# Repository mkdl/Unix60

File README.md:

# Unix60
The Unix60 is a budget FR4 keyboard designed to make a HHKB-style layout available to everyone with as few compromises as possible.

If you have any questions or need help, please join the FR4 Discord: https://discord.gg/z7mpQX5YJQ

### Disclaimer: You must follow this guide in the order it is written. Assembling stuff in the wrong order (specifically your Pro Micro or Elite C and its headers) will likely result in you having to desolder components and significantly increase the amount of time it takes to assemble. I am not responsible for boards damaged during assembly. I highly recommend you read through the entire guide before starting assembly.

# Assembly:

### 1. Put the diodes through the PCB so the legs stick out the front side of the board and so the diode is flush with the back, making sure the black line on the diode faces the square pad:

### 2. Solder from the back and snip the legs:

### 3. Place your Pro Micro or Elite C onto its pin headers and sit it into the board so the Pro Micro is on the back of the PCB (the side with the Unix60 logo) and tape it down to temporarily hold it in place. This helps align the pin headers properly. It doesn't matter whether you put the shorter pins on the PCB or the longer ones; either way, you will have to snip the longer ones once you've soldered them in. **DO NOT SOLDER THE PRO MICRO OR ELITE C TO THE PIN HEADERS YET!**

### 4. Solder in the pin headers from the front side of the PCB. **Do not solder the Pro Micro or Elite C yet, just the headers!**

### 5. Solder your reset button to the PCB 

### Note: If you've lost your reset button, don't worry. Shorting the two pads closest to the edge of the PCB or the two closest to the inside will reset your controller. After all, that's all the button does :)
### 8. Attach your stabs to the PCB (do not be afraid to push, you won't break it)

### 9. Mount switches in the corner of the plate to align it, then lower the plate onto the PCB

### 10. Add the rest of your switches and solder them all in

### 11. Once you have verified that all your diodes, switches, and Pro Micro or Elite C pin headers are soldered properly, you can now solder your Pro Micro or Elite C onto the pin headers:

### 12. Attach standoffs to the bottom of the plate using screws from the other side, you may need to cut of the long pins on your controller board if the bottom plate wont fit on.

### 13. Screw on the bottom plate
# Flashing instructions for Linux:
### 1. Plug your Pro Micro or Elite C in
### 2. Open up the [QMK configurator](https://config.qmk.fm/#/fr4/unix60/LAYOUT_all) and create your desired layout
### 3. Download the .json file (on the left, next to keymap.json)
### 4. Open up a command line
### 5. Type ```qmk flash /path/to/layout.json``` (obviously replacing the file path with the path to your downloaded layout) and follow any additional instructions
### One thing to note is that you can compile a .hex file on the configurator and flash that with avrdude, however, I prefer the method outlined above.
# Flashing instructions for Windows:
### Please keep in mind that I do not run Windows on my own system and cannot 100% verify this flashing procedure will work or if it requires any other configuration. I highly recommend you check the QMK docs if something is not working. 
### 1. Plug your Pro Micro or Elite C in
### 2. Open up the [QMK configurator](https://config.qmk.fm/#/fr4/unix60/LAYOUT_all) and create your desired layout
### 3. Click "compile" in the upper right, and once it's done, download the .hex by clicking "firmware"
### 4. Open up [QMK toolbox](https://github.com/qmk/qmk_toolbox/releases) and load your downloaded .hex
### 5. Click "flash" and follow any additional instructions - you may need to click reset for QMK Toolbox to figure out there is a flashable device.

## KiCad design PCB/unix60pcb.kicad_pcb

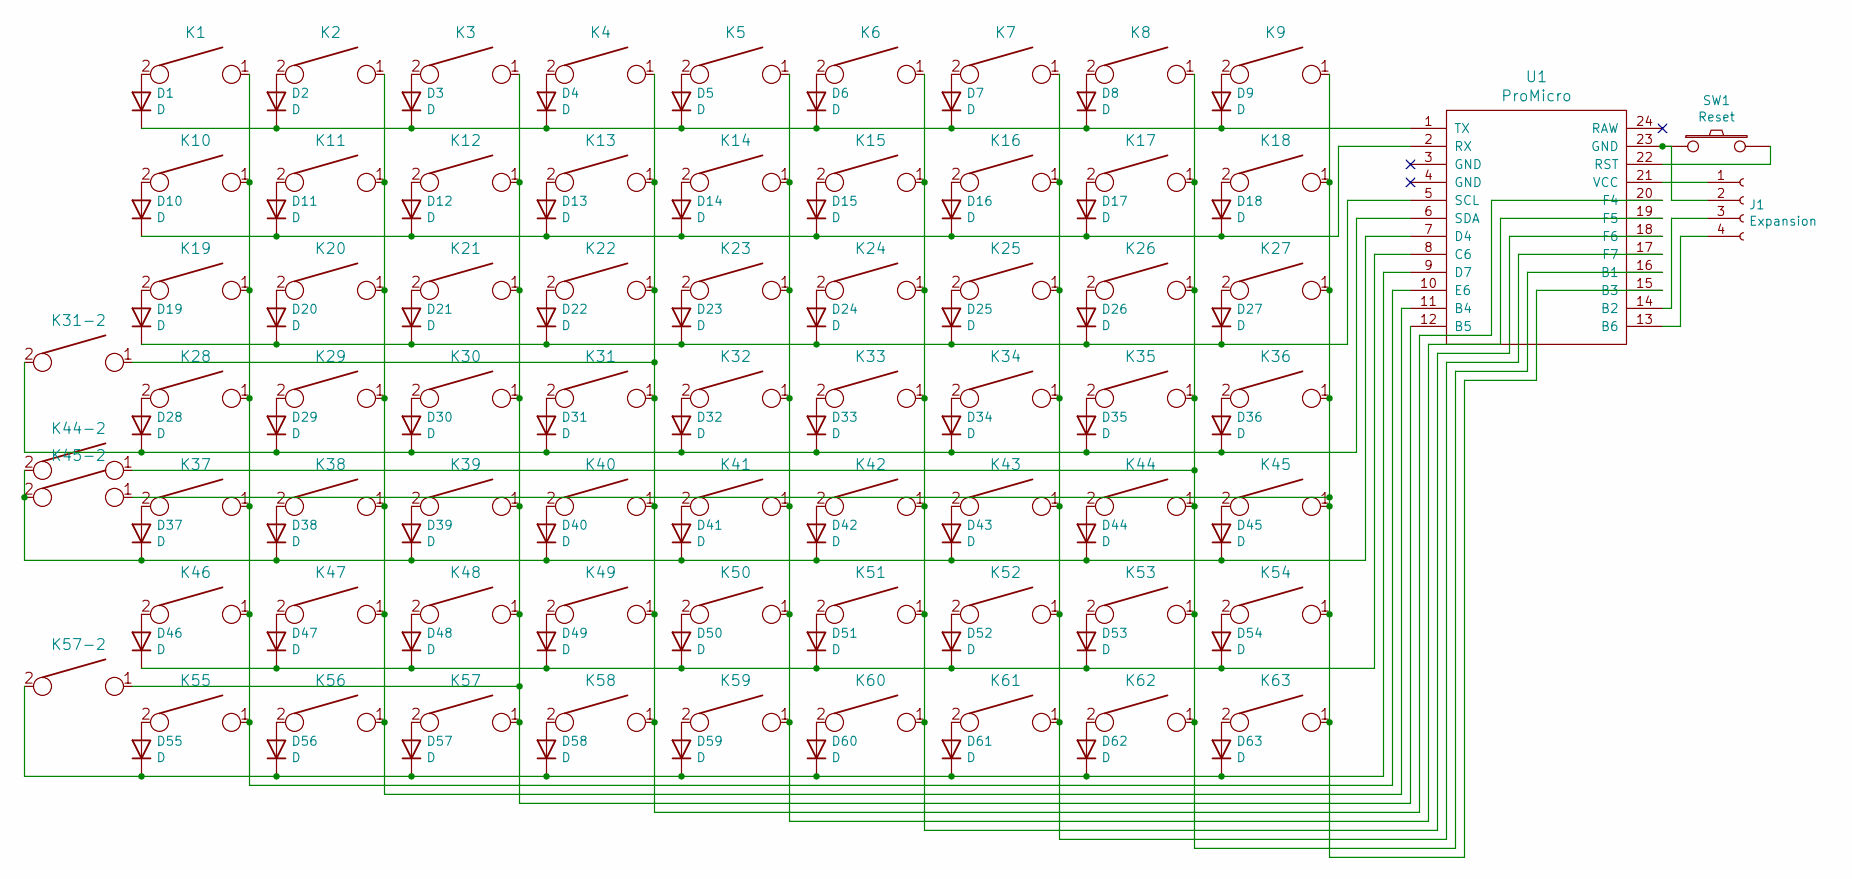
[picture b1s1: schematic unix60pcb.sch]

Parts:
D1, D2, D3, D4, D5, D6, D7, D8, D9, D10, D11, D12, D13, D14, D15, D16, D17, D18, D19, D20, D21, D22, D23, D24, D25, D26, D27, D28, D29, D30, D31, D32, D33, D34, D35, D36, D37, D38, D39, D40, D41, D42, D43, D44, D45, D46, D47, D48, D49, D50, D51, D52, D53, D54, D55, D56, D57, D58, D59, D60, D61, D62, D63: D; D_SOD123_axial-dual
J1: Expansion; PinSocket_1x04_P2.54mm_Vertical
K1, K2, K3, K4, K5, K6, K7, K8, K9, K10, K11, K12, K13, K14, K16, K18, K19, K20, K21, K22, K23, K24, K25, K26, K27, K28, K29, K32, K33, K34, K35, K36, K37, K38, K39, K40, K41, K42, K43, K46, K47, K48, K49, K50, K51, K52, K53, K54, K55, K56, K58, K59, K63: KEYSW; MXOnly-1U-NoLED
K15: KEYSW; MXOnly-2U-NoLED
K17, K30, K60, K62: KEYSW; MXOnly-1.5U-NoLED
K31, K57-2: KEYSW; MXOnly-1.75U-NoLED
K31-2, K45-2: KEYSW; MXOnly-1.25U-NoLED
K44, K45: KEYSW; MXOnly-2.25U-NoLED
K44-2: KEYSW; MXOnly-ISO-ROTATED-ReversedStabilizers-NoLED
K57: KEYSW; MXOnly-2.75U-NoLED
K61: KEYSW; MXOnly-7U-NoLED
SW1: Reset; SW_SPST_TL3342
U1: ProMicro

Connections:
unnamed: D1.1 (K), D2.1 (K), D3.1 (K), D4.1 (K), D5.1 (K), D6.1 (K), D7.1 (K), D8.1 (K), D9.1 (K), U1.1 (TX)
unnamed: D1.2 (A), K1.2
unnamed: D2.2 (A), K2.2
unnamed: D3.2 (A), K3.2
unnamed: D4.2 (A), K4.2
unnamed: D5.2 (A), K5.2
unnamed: D6.2 (A), K6.2
unnamed: D7.2 (A), K7.2
unnamed: D8.2 (A), K8.2
unnamed: D9.2 (A), K9.2
unnamed: D10.1 (K), D11.1 (K), D12.1 (K), D13.1 (K), D14.1 (K), D15.1 (K), D16.1 (K), D17.1 (K), D18.1 (K), U1.2 (RX)
unnamed: D10.2 (A), K10.2
unnamed: D11.2 (A), K11.2
unnamed: D12.2 (A), K12.2
unnamed: D13.2 (A), K13.2
unnamed: D14.2 (A), K14.2
unnamed: D15.2 (A), K15.2
unnamed: D16.2 (A), K16.2
unnamed: D17.2 (A), K17.2
unnamed: D18.2 (A), K18.2
unnamed: D19.1 (K), D20.1 (K), D21.1 (K), D22.1 (K), D23.1 (K), D24.1 (K), D25.1 (K), D26.1 (K), D27.1 (K), U1.5 (SCL)
unnamed: D19.2 (A), K19.2
unnamed: D20.2 (A), K20.2
unnamed: D21.2 (A), K21.2
unnamed: D22.2 (A), K22.2
unnamed: D23.2 (A), K23.2
unnamed: D24.2 (A), K24.2
unnamed: D25.2 (A), K25.2
unnamed: D26.2 (A), K26.2
unnamed: D27.2 (A), K27.2
unnamed: D28.1 (K), D29.1 (K), D30.1 (K), D31.1 (K), D32.1 (K), D33.1 (K), D34.1 (K), D35.1 (K), D36.1 (K), K31-2.2, U1.6 (SDA)
unnamed: D28.2 (A), K28.2
unnamed: D29.2 (A), K29.2
unnamed: D30.2 (A), K30.2
unnamed: D31.2 (A), K31.2
unnamed: D32.2 (A), K32.2
unnamed: D33.2 (A), K33.2
unnamed: D34.2 (A), K34.2
unnamed: D35.2 (A), K35.2
unnamed: D36.2 (A), K36.2
unnamed: D37.1 (K), D38.1 (K), D39.1 (K), D40.1 (K), D41.1 (K), D42.1 (K), D43.1 (K), D44.1 (K), D45.1 (K), K44-2.2, K45-2.2, U1.7 (D4)
unnamed: D37.2 (A), K37.2
unnamed: D38.2 (A), K38.2
unnamed: D39.2 (A), K39.2
unnamed: D40.2 (A), K40.2
unnamed: D41.2 (A), K41.2
unnamed: D42.2 (A), K42.2
unnamed: D43.2 (A), K43.2
unnamed: D44.2 (A), K44.2
unnamed: D45.2 (A), K45.2
unnamed: D46.1 (K), D47.1 (K), D48.1 (K), D49.1 (K), D50.1 (K), D51.1 (K), D52.1 (K), D53.1 (K), D54.1 (K), U1.8 (C6)
unnamed: D46.2 (A), K46.2
unnamed: D47.2 (A), K47.2
unnamed: D48.2 (A), K48.2
unnamed: D49.2 (A), K49.2
unnamed: D50.2 (A), K50.2
unnamed: D51.2 (A), K51.2
unnamed: D52.2 (A), K52.2
unnamed: D53.2 (A), K53.2
unnamed: D54.2 (A), K54.2
unnamed: D55.1 (K), D56.1 (K), D57.1 (K), D58.1 (K), D59.1 (K), D60.1 (K), D61.1 (K), D62.1 (K), D63.1 (K), K57-2.2, U1.9 (D7)
unnamed: D55.2 (A), K55.2
unnamed: D56.2 (A), K56.2
unnamed: D57.2 (A), K57.2
unnamed: D58.2 (A), K58.2
unnamed: D59.2 (A), K59.2
unnamed: D60.2 (A), K60.2
unnamed: D61.2 (A), K61.2
unnamed: D62.2 (A), K62.2
unnamed: D63.2 (A), K63.2
unnamed: J1.1, U1.21 (VCC)
unnamed: J1.2, SW1.1, U1.23 (GND)
unnamed: J1.3, U1.14 (B2)
unnamed: J1.4, U1.13 (B6)
unnamed: K1.1, K10.1, K19.1, K28.1, K37.1, K46.1, K55.1, U1.10 (E6)
unnamed: K2.1, K11.1, K20.1, K29.1, K38.1, K47.1, K56.1, U1.11 (B4)
unnamed: K3.1, K12.1, K21.1, K30.1, K39.1, K48.1, K57.1, K57-2.1, U1.12 (B5)
unnamed: K4.1, K13.1, K22.1, K31.1, K31-2.1, K40.1, K49.1, K58.1, U1.20 (F4)
unnamed: K5.1, K14.1, K23.1, K32.1, K41.1, K50.1, K59.1, U1.19 (F5)
unnamed: K6.1, K15.1, K24.1, K33.1, K42.1, K51.1, K60.1, U1.18 (F6)
unnamed: K7.1, K16.1, K25.1, K34.1, K43.1, K52.1, K61.1, U1.17 (F7)
unnamed: K8.1, K17.1, K26.1, K35.1, K44.1, K44-2.1, K53.1, K62.1, U1.16 (B1)
unnamed: K9.1, K18.1, K27.1, K36.1, K45.1, K45-2.1, K54.1, K63.1, U1.15 (B3)
unnamed: SW1.2, U1.22 (RST)

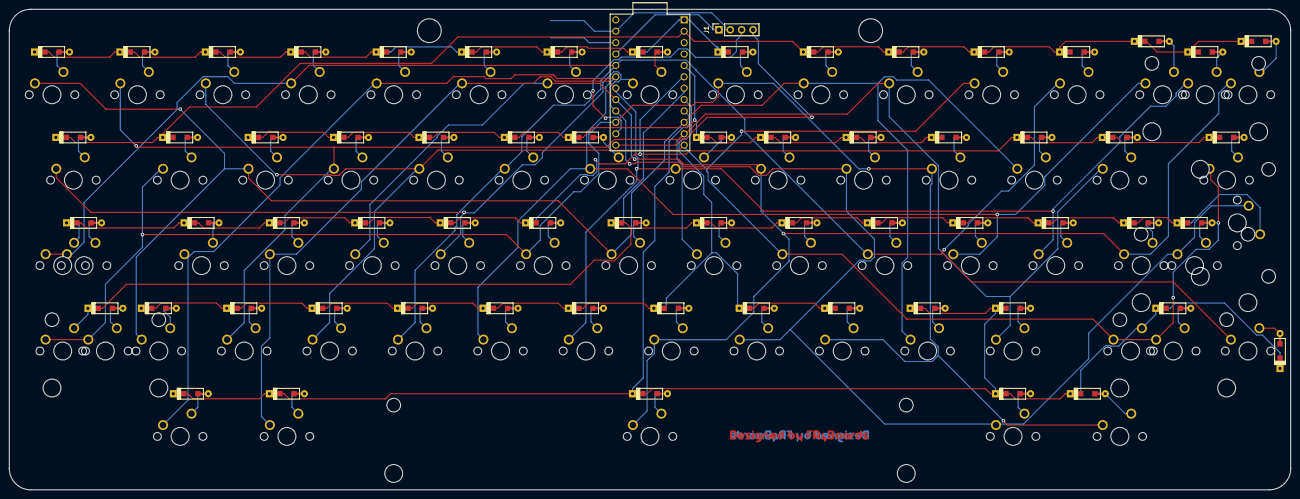
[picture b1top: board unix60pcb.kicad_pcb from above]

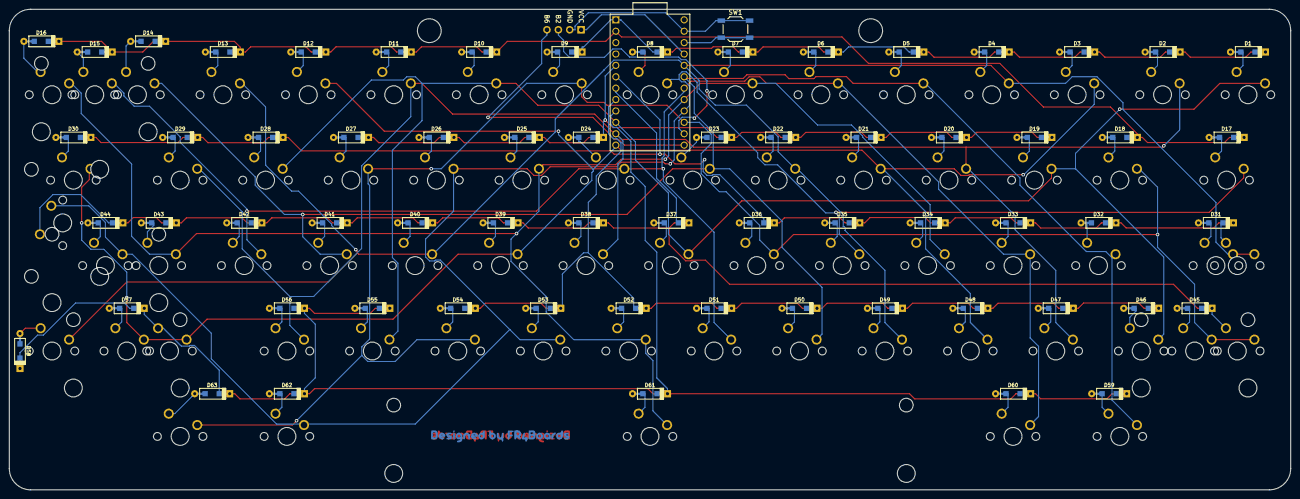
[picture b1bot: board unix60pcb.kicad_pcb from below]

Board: 2 copper layers, 285.8 x 107.2 mm, 133 parts (65 on the bottom side), 84 nets.

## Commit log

2020-12-09 adding unix60
2020-12-09 Added Pictures
2020-12-09 added guide
2021-03-09 Added QMK and Via firmware files
2021-03-09 fixed links to config.qmk.fm
2021-03-13 Adding a license
2021-05-08 small changes after run thru
    pins may need to be clipped on microcontroller, and link to qmk toolbox for windows
2021-09-17 Use holes for standoffs instead of wide cutouts on the PCB
2021-09-17 Update gerbers
2021-09-17 Use nicer, correctly sized plate cutouts; clean up edge plating
2021-09-17 Add bottom plate feet mounting holes; clean up edge plating
